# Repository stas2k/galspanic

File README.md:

# GALSPanic - X68000 SRAM Expansion

This repo contains Kicad sources for a Static RAM expansion board for Sharp X68000 personal computer.
Please use latest git version of kicad to open the project, or version >6.0 once it gets released.

## Design
The expansion is implemented using 2MB static RAM chips to make the design simpler.
Address decoder is implemented using a ATF22V10 GAL chip. Source code for it is available in `gal/` directory.

Board dimensions are taken from the [midiori](https://github.com/tdaede/midiori) project.

The board can support up to 10MB of memory and assumes you already have 2MB built in.

A fourth address line is routed and the board can support 1MB systems by masking half of the first memory chip. However, the GAL equations are not written for this case. Let me know if you have such a system.

## Compatibility
Following systems have been reported to work:
- Super
- Expert
- ACE
- XVI
- Pro
- 68030

## GAL Equations

You can compile `.pld` GAL equations using [GALasm](https://github.com/daveho/GALasm).

## Board production

I use JLCPCB with the following options:
* PCB Thickness: 1.6
* Surface Finish: ENIG-RoHS
* Gold Fingers: Yes
* 45°finger chamfered: Yes

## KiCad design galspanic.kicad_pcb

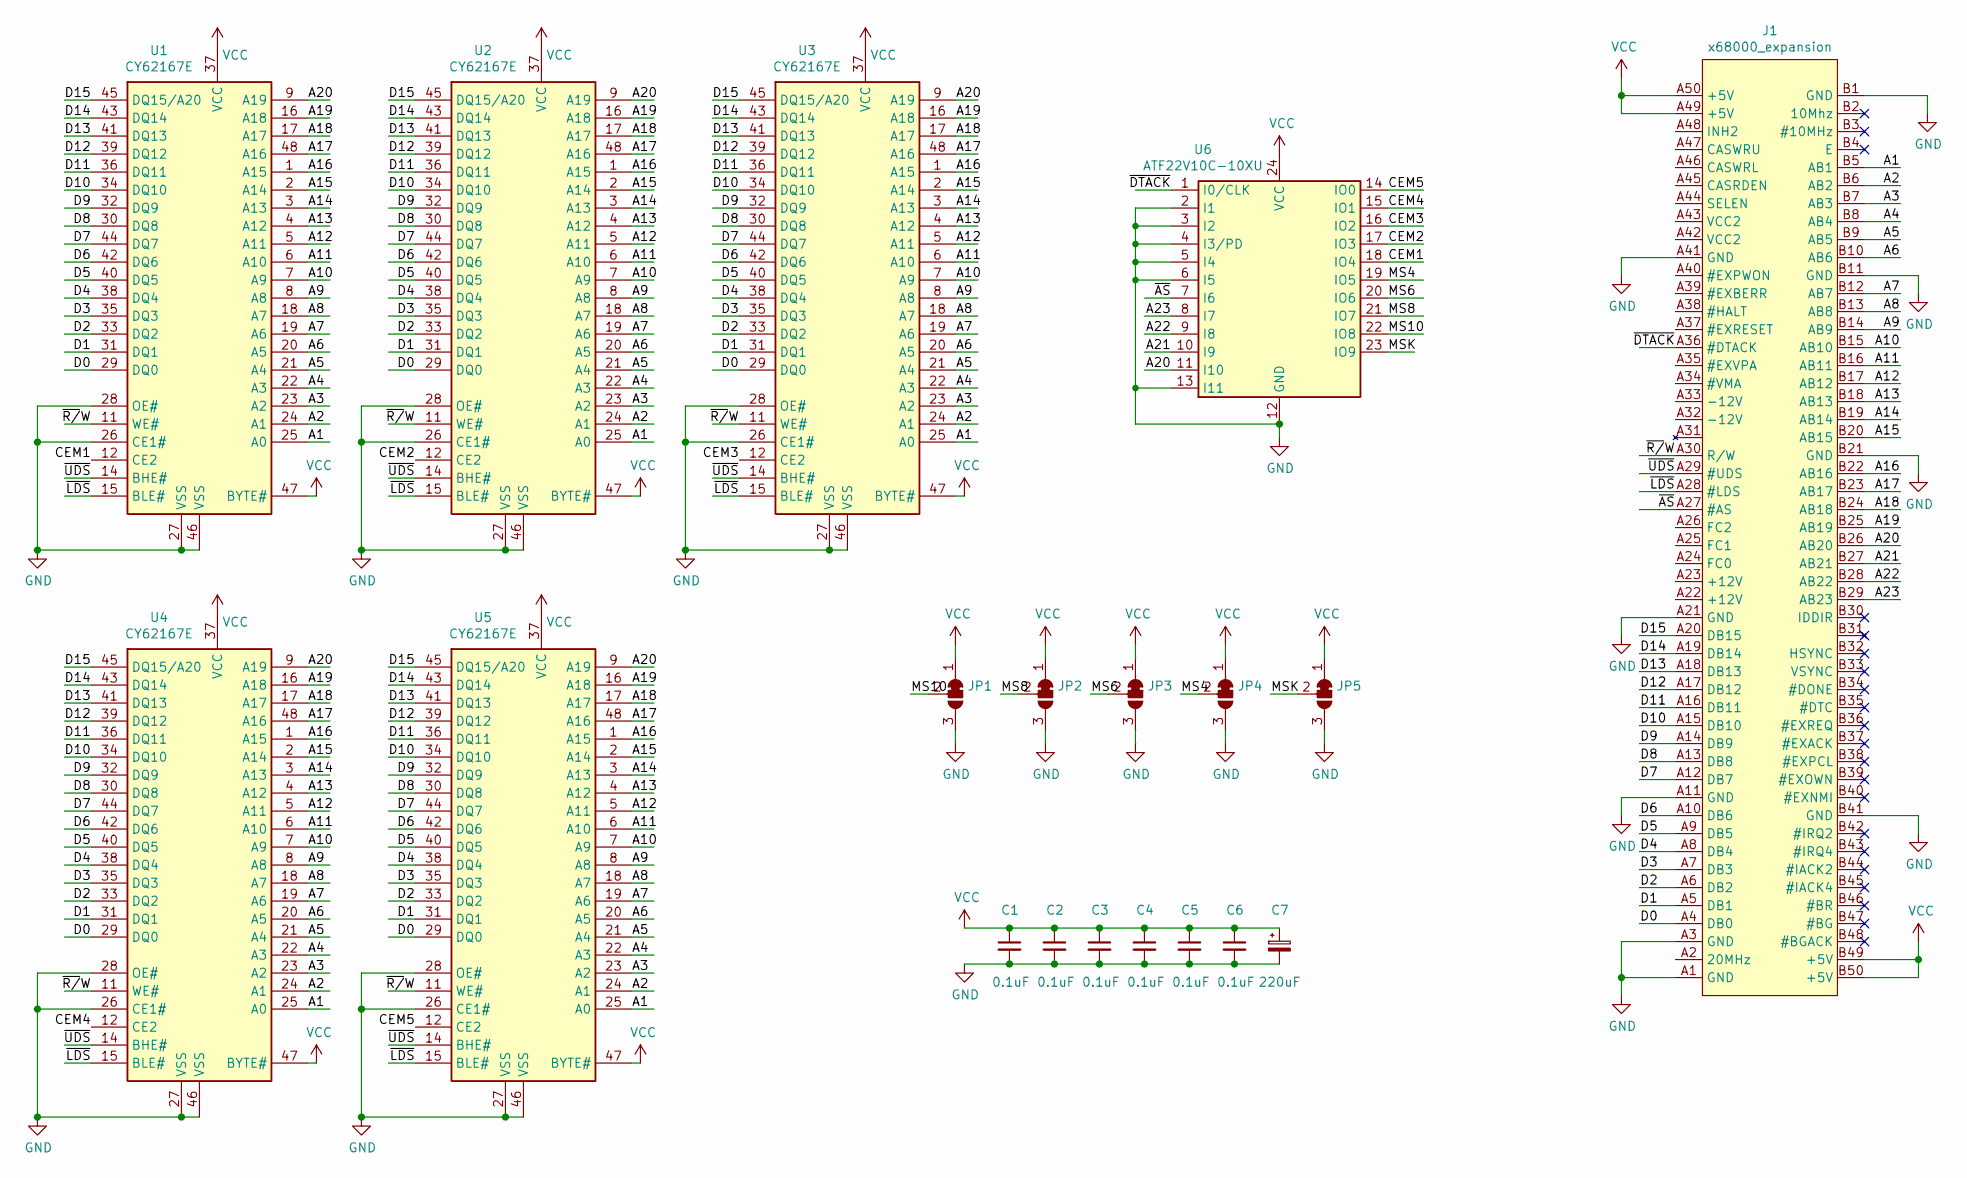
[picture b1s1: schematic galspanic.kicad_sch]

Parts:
C1, C2, C3, C4, C5, C6: 0.1uF; C_0603_1608Metric_Pad1.08x0.95mm_HandSolder
C7: 220uF; CP_Radial_D6.3mm_P2.50mm
J1: x68000_expansion
JP1, JP2, JP3, JP4, JP5: SolderJumper_3_Bridged12; SolderJumper-3_P1.3mm_Bridged12_RoundedPad1.0x1.5mm
U1, U2, U3, U4, U5: CY62167E; TSOP-I-48_18.4x12mm_P0.5mm
U6: ATF22V10C-10XU; TSSOP-24_4.4x7.8mm_P0.65mm

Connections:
/A1: J1.B5 (AB1), U1.25 (A0), U2.25 (A0), U3.25 (A0), U4.25 (A0), U5.25 (A0)
/A2: J1.B6 (AB2), U1.24 (A1), U2.24 (A1), U3.24 (A1), U4.24 (A1), U5.24 (A1)
/A3: J1.B7 (AB3), U1.23 (A2), U2.23 (A2), U3.23 (A2), U4.23 (A2), U5.23 (A2)
/A4: J1.B8 (AB4), U1.22 (A3), U2.22 (A3), U3.22 (A3), U4.22 (A3), U5.22 (A3)
/A5: J1.B9 (AB5), U1.21 (A4), U2.21 (A4), U3.21 (A4), U4.21 (A4), U5.21 (A4)
/A6: J1.B10 (AB6), U1.20 (A5), U2.20 (A5), U3.20 (A5), U4.20 (A5), U5.20 (A5)
/A7: J1.B12 (AB7), U1.19 (A6), U2.19 (A6), U3.19 (A6), U4.19 (A6), U5.19 (A6)
/A8: J1.B13 (AB8), U1.18 (A7), U2.18 (A7), U3.18 (A7), U4.18 (A7), U5.18 (A7)
/A9: J1.B14 (AB9), U1.8 (A8), U2.8 (A8), U3.8 (A8), U4.8 (A8), U5.8 (A8)
/A10: J1.B15 (AB10), U1.7 (A9), U2.7 (A9), U3.7 (A9), U4.7 (A9), U5.7 (A9)
/A11: J1.B16 (AB11), U1.6 (A10), U2.6 (A10), U3.6 (A10), U4.6 (A10), U5.6 (A10)
/A12: J1.B17 (AB12), U1.5 (A11), U2.5 (A11), U3.5 (A11), U4.5 (A11), U5.5 (A11)
/A13: J1.B18 (AB13), U1.4 (A12), U2.4 (A12), U3.4 (A12), U4.4 (A12), U5.4 (A12)
/A14: J1.B19 (AB14), U1.3 (A13), U2.3 (A13), U3.3 (A13), U4.3 (A13), U5.3 (A13)
/A15: J1.B20 (AB15), U1.2 (A14), U2.2 (A14), U3.2 (A14), U4.2 (A14), U5.2 (A14)
/A16: J1.B22 (AB16), U1.1 (A15), U2.1 (A15), U3.1 (A15), U4.1 (A15), U5.1 (A15)
/A17: J1.B23 (AB17), U1.48 (A16), U2.48 (A16), U3.48 (A16), U4.48 (A16), U5.48 (A16)
/A18: J1.B24 (AB18), U1.17 (A17), U2.17 (A17), U3.17 (A17), U4.17 (A17), U5.17 (A17)
/A19: J1.B25 (AB19), U1.16 (A18), U2.16 (A18), U3.16 (A18), U4.16 (A18), U5.16 (A18)
/A20: J1.B26 (AB20), U1.9 (A19), U2.9 (A19), U3.9 (A19), U4.9 (A19), U5.9 (A19), U6.11 (I10)
/A21: J1.B27 (AB21), U6.10 (I9)
/A22: J1.B28 (AB22), U6.9 (I8)
/A23: J1.B29 (AB23), U6.8 (I7)
/CEM1: U1.12 (CE2), U6.18 (IO4)
/CEM2: U2.12 (CE2), U6.17 (IO3)
/CEM3: U3.12 (CE2), U6.16 (IO2)
/CEM4: U4.12 (CE2), U6.15 (IO1)
/CEM5: U5.12 (CE2), U6.14 (IO0)
/D0: J1.A4 (DB0), U1.29 (DQ0), U2.29 (DQ0), U3.29 (DQ0), U4.29 (DQ0), U5.29 (DQ0)
/D1: J1.A5 (DB1), U1.31 (DQ1), U2.31 (DQ1), U3.31 (DQ1), U4.31 (DQ1), U5.31 (DQ1)
/D2: J1.A6 (DB2), U1.33 (DQ2), U2.33 (DQ2), U3.33 (DQ2), U4.33 (DQ2), U5.33 (DQ2)
/D3: J1.A7 (DB3), U1.35 (DQ3), U2.35 (DQ3), U3.35 (DQ3), U4.35 (DQ3), U5.35 (DQ3)
/D4: J1.A8 (DB4), U1.38 (DQ4), U2.38 (DQ4), U3.38 (DQ4), U4.38 (DQ4), U5.38 (DQ4)
/D5: J1.A9 (DB5), U1.40 (DQ5), U2.40 (DQ5), U3.40 (DQ5), U4.40 (DQ5), U5.40 (DQ5)
/D6: J1.A10 (DB6), U1.42 (DQ6), U2.42 (DQ6), U3.42 (DQ6), U4.42 (DQ6), U5.42 (DQ6)
/D7: J1.A12 (DB7), U1.44 (DQ7), U2.44 (DQ7), U3.44 (DQ7), U4.44 (DQ7), U5.44 (DQ7)
/D8: J1.A13 (DB8), U1.30 (DQ8), U2.30 (DQ8), U3.30 (DQ8), U4.30 (DQ8), U5.30 (DQ8)
/D9: J1.A14 (DB9), U1.32 (DQ9), U2.32 (DQ9), U3.32 (DQ9), U4.32 (DQ9), U5.32 (DQ9)
/D10: J1.A15 (DB10), U1.34 (DQ10), U2.34 (DQ10), U3.34 (DQ10), U4.34 (DQ10), U5.34 (DQ10)
/D11: J1.A16 (DB11), U1.36 (DQ11), U2.36 (DQ11), U3.36 (DQ11), U4.36 (DQ11), U5.36 (DQ11)
/D12: J1.A17 (DB12), U1.39 (DQ12), U2.39 (DQ12), U3.39 (DQ12), U4.39 (DQ12), U5.39 (DQ12)
/D13: J1.A18 (DB13), U1.41 (DQ13), U2.41 (DQ13), U3.41 (DQ13), U4.41 (DQ13), U5.41 (DQ13)
/D14: J1.A19 (DB14), U1.43 (DQ14), U2.43 (DQ14), U3.43 (DQ14), U4.43 (DQ14), U5.43 (DQ14)
/D15: J1.A20 (DB15), U1.45 (DQ15/A20), U2.45 (DQ15/A20), U3.45 (DQ15/A20), U4.45 (DQ15/A20), U5.45 (DQ15/A20)
/MS4: JP4.2 (C), U6.19 (IO5)
/MS6: JP3.2 (C), U6.20 (IO6)
/MS8: JP2.2 (C), U6.21 (IO7)
/MS10: JP1.2 (C), U6.22 (IO8)
/MSK: JP5.2 (C), U6.23 (IO9)
/~AS: J1.A27 (#AS), U6.7 (I6)
/~DTACK: J1.A36 (#DTACK), U6.1 (I0/CLK)
/~LDS: J1.A28 (#LDS), U1.15 (BLE#), U2.15 (BLE#), U3.15 (BLE#), U4.15 (BLE#), U5.15 (BLE#)
/~R/W: J1.A30 (R/W), U1.11 (WE#), U2.11 (WE#), U3.11 (WE#), U4.11 (WE#), U5.11 (WE#)
/~UDS: J1.A29 (#UDS), U1.14 (BHE#), U2.14 (BHE#), U3.14 (BHE#), U4.14 (BHE#), U5.14 (BHE#)
GND: C1.2, C2.2, C3.2, C4.2, C5.2, C6.2, C7.2, J1.A1 (GND), J1.A3 (GND), J1.A11 (GND), J1.A21 (GND), J1.A41 (GND), J1.B1 (GND), J1.B11 (GND), J1.B21 (GND), J1.B41 (GND), JP1.3 (B), JP2.3 (B), JP3.3 (B), JP4.3 (B), JP5.3 (B), U1.26 (CE1#), U1.27 (VSS), U1.28 (OE#), U1.46 (VSS), U2.26 (CE1#), U2.27 (VSS), U2.28 (OE#), U2.46 (VSS), U3.26 (CE1#), U3.27 (VSS), U3.28 (OE#), U3.46 (VSS), U4.26 (CE1#), U4.27 (VSS), U4.28 (OE#), U4.46 (VSS), U5.26 (CE1#), U5.27 (VSS), U5.28 (OE#), U5.46 (VSS), U6.2 (I1), U6.3 (I2), U6.4 (I3/PD), U6.5 (I4), U6.6 (I5), U6.12 (GND), U6.13 (I11)
VCC: C1.1, C2.1, C3.1, C4.1, C5.1, C6.1, C7.1, J1.A49 (+5V), J1.A50 (+5V), J1.B49 (+5V), J1.B50 (+5V), JP1.1 (A), JP2.1 (A), JP3.1 (A), JP4.1 (A), JP5.1 (A), U1.37 (VCC), U1.47 (BYTE#), U2.37 (VCC), U2.47 (BYTE#), U3.37 (VCC), U3.47 (BYTE#), U4.37 (VCC), U4.47 (BYTE#), U5.37 (VCC), U5.47 (BYTE#), U6.24 (VCC)

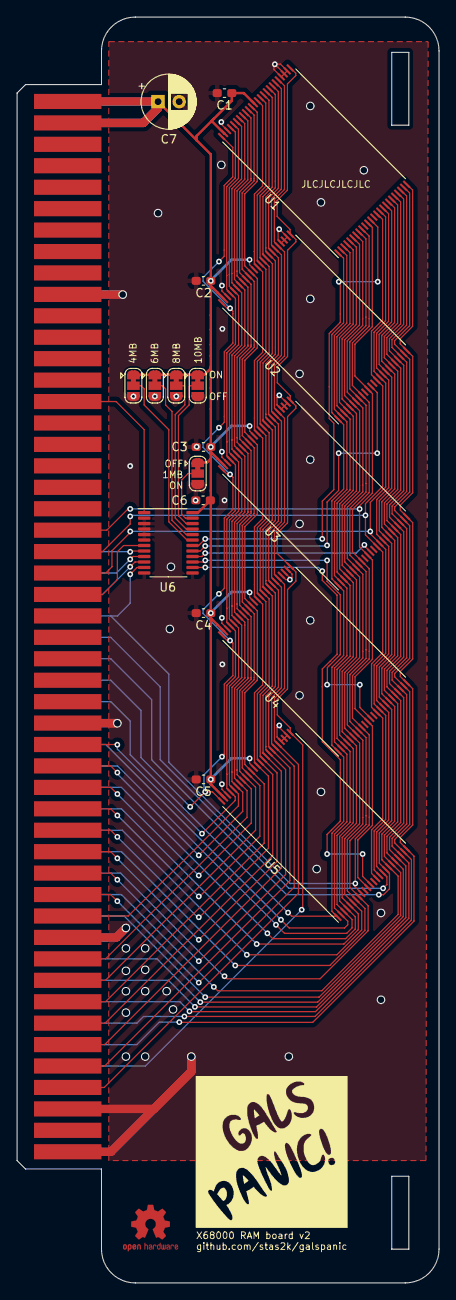
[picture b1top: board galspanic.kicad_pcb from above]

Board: 2 copper layers, 50.0 x 149.9 mm, 19 parts (0 on the bottom side), 56 nets.

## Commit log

2020-09-10 first upload
2020-09-10 add info on gal
2020-09-12 route A20, fix power cap footprint
2020-09-12 readme: add production info
2020-09-14 Add MIT license
2020-09-23 Update README.md
    add XVI as tested
2020-09-23 Update README.md
    add 1MB system information
2020-09-25 gal: add 4MB board
2020-09-25 pcb: add grounding around A20
2020-09-25 readme: update board image
2020-10-06 add ACE system to README
2020-12-10 update board image
2020-12-27 upgrade kicad
2021-01-28 gal: add 6MB board
2021-01-28 pcb: add memory size jumpers
2021-01-28 gal: add configurable memory size
2021-01-28 pcb: v1.2 release
2021-10-15 release a smaller board with no buffers
2022-02-16 README: Fix midiori spelling, add 68030 note
2022-02-21 gal: have a single GAL pld file
2022-03-18 README: add Super model compat info
2025-11-24 gal: use tri-state output for DTACK to avoid bus contention
    Changed DTACK from push-pull output to tri-state output using the
    GAL's output enable (.E) function. This allows the pin to pull the
    line low when memory is accessed, and go high-impedance otherwise,
    preventing the GAL from fighting other devices on the shared bus.
